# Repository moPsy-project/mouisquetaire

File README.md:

# Mousquetaire Eurorack Module

> Eurorack Synthesizer module for Audio/CV Adder and Buffered Multiple

## Dependencies

This project uses symbols from the [moPsy-KiCad-resources](https://github.com/moPsy-project/moPsy-KiCad-resources).

## License

This work is licensed under a [Creative Commons Attribution-ShareAlike 4.0 International License](http://creativecommons.org/licenses/by-sa/4.0/).

BY: Stefan Haun (mail@tuxathome.de)

See [LICENSE.txt](LICENSE.txt) for details.

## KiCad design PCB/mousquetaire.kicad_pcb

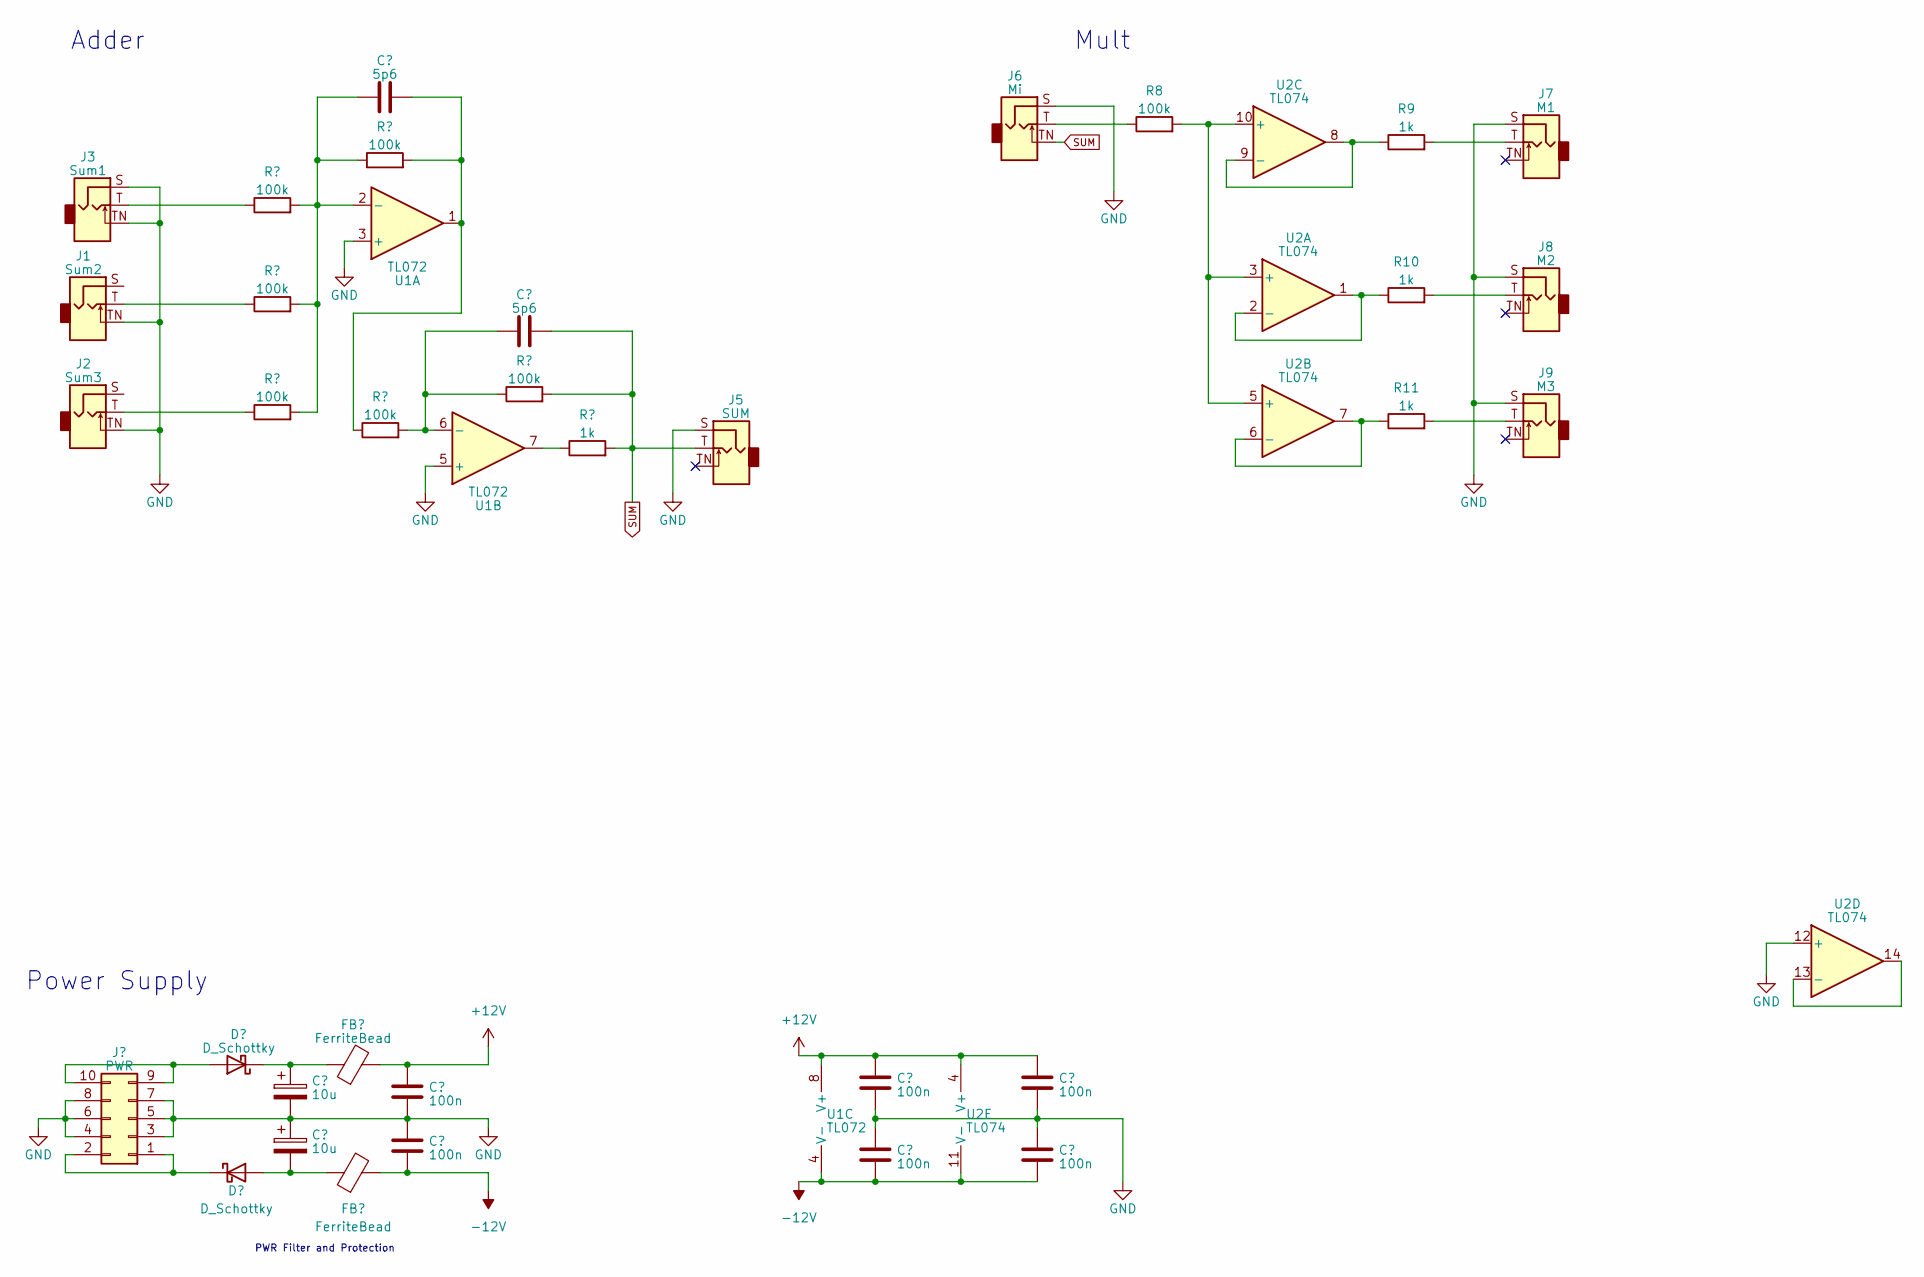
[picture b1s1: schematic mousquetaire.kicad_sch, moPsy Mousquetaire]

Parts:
C1, C2: 10u; CP_Radial_D4.0mm_P1.50mm
C3, C6: 5p6; C_Disc_D4.3mm_W1.9mm_P5.00mm
C4, C5, C7, C8, C9, C10: 100n; C_Disc_D4.3mm_W1.9mm_P5.00mm
D1, D2: D_Schottky; D_DO-41_SOD81_P7.62mm_Horizontal
FB1, FB2: FerriteBead; FBeadL4D4
J1: Sum2; CLIFF 3.5mm S6 Mono Jack Socket
J2: Sum3; CLIFF 3.5mm S6 Mono Jack Socket
J3: Sum1; CLIFF 3.5mm S6 Mono Jack Socket
J4: PWR; PinHeader_2x05_P2.54mm_Vertical
J5: SUM; CLIFF 3.5mm S6 Mono Jack Socket
J6: Mi; CLIFF 3.5mm S6 Mono Jack Socket
J7: M1; CLIFF 3.5mm S6 Mono Jack Socket
J8: M2; CLIFF 3.5mm S6 Mono Jack Socket
J9: M3; CLIFF 3.5mm S6 Mono Jack Socket
R1, R2, R3, R4, R5, R6, R8: 100k; R_Axial_DIN0207_L6.3mm_D2.5mm_P7.62mm_Horizontal
R7, R9, R10, R11: 1k; R_Axial_DIN0207_L6.3mm_D2.5mm_P7.62mm_Horizontal
U1: TL072; DIP-8_W7.62mm_Socket_LongPads
U2: TL074; DIP-14_W7.62mm_Socket_LongPads

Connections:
+12V: C4.1, C7.1, C9.1, FB1.2, U1.8 (V+), U2.4 (V+)
-12V: C5.2, C8.2, C10.2, FB2.2, U1.4 (V-), U2.11 (V-)
GND: C1.2, C2.1, C4.2, C5.1, C7.2, C8.1, C9.2, C10.1, J1.TN, J2.TN, J3.S, J3.TN, J4.3, J4.4, J4.5, J4.6, J4.7, J4.8, J5.S, J6.S, J7.S, J8.S, J9.S, U1.3 (+), U1.5 (+), U2.12 (+)
unnamed: C3.2, R4.1, R5.2, U1.1
unnamed: D1.2 (A), J4.9, J4.10
unnamed: C1.1, D1.1 (K), FB1.1
unnamed: C2.2, D2.2 (A), FB2.1
unnamed: D2.1 (K), J4.1, J4.2
unnamed: J1.T, R2.1
unnamed: J2.T, R3.1
unnamed: J3.T, R1.1
unnamed: J6.T, R8.1
unnamed: J7.T, R9.2
unnamed: J8.T, R10.2
unnamed: J9.T, R11.2
unnamed: R7.1, U1.7
unnamed: C3.1, R1.2, R2.2, R3.2, R5.1, U1.2 (-)
unnamed: C6.1, R4.2, R6.1, U1.6 (-)
unnamed: R8.2, U2.3 (+), U2.5 (+), U2.10 (+)
unnamed: R10.1, U2.1, U2.2 (-)
unnamed: R11.1, U2.6 (-), U2.7
unnamed: R9.1, U2.8, U2.9 (-)
unnamed: U2.13 (-), U2.14
SUM: C6.2, J5.T, J6.TN, R6.2, R7.2

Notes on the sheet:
Adder
Mult
Power Supply
PWR Filter and Protection

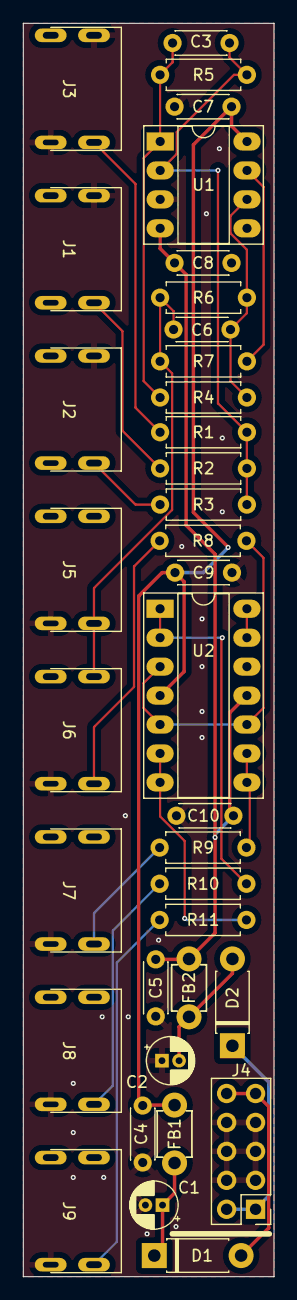
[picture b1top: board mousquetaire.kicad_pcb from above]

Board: 2 copper layers, 22.0 x 110.0 mm, 36 parts (0 on the bottom side), 24 nets.

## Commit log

2023-04-16 :tada: Initial commit
2023-04-16 :page_facing_up: Add LICENSE and Dependency information
2023-04-16 :money_with_wings: Add FUNDING information
2023-04-16 :construction_worker: Add release workflow
2023-04-16 :see_no_evil: Add gitignore for KiCad project
2023-04-16 :bento: Add DXF export of outline
2023-04-16 :sparkles: Add KiCad project and schematic draft
2023-04-16 :sparkles: Add frontpanel outline as FreeCad sketch
2023-04-16 :sparkles: Add draft for the PCB layout
2023-04-20 :pencil2: Fix the adder circuit
2023-04-20 :pencil2: Add missing changes for the adder fix
    Somehow not everything had been committed for #2. This is the fix. :/
2023-04-20 :sparkles: Route traces on the PCB
2023-04-20 :hammer: Set up project for PCB design
2023-04-20 :hammer: Adjust layout after fixing the schematic
2023-04-20 :art: Improvements to schematic for PCB design
    Mostly interchanging components for easier routing.
2023-04-20 :hammer: Change power connector to vertical footprint
2023-04-20 :hammer: Turn power connector around and adapt to footprint
    Move the power connector so that the red stripe is down.
